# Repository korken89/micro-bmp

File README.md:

# Micro Black Magic Probe (µBMP)

A small [Black Magic Probe](https://github.com/blacksphere/blackmagic) based on the pinout of the STLink V2 support firmware. Connections has been added for the support of SWO, while the UART pinout is also available. Designed to stick directly into a USB port, without cable.

## Changes

### v1.4.1

* Reinforced the USB-C plug's mounting pads

### v1.4

* Changed to USB-C plug

### v1.3

* Added LED on the 5V line to see when the fuse is "blown"
* Removed panelized boards, to be updated later

### v1.2

* Removed component designators to clean up the PCB, the designators are available in the Gerbers
* Consolidated components, using resistor arrays and 8ch ESD/EMI filter
* Now have ESD/EMI protection on the outputs
* Added fuse of 5V line

### v1.0

* First release
* Tested and working

## Resources

### Schematics

A PDF print of the schematic are available in `ubmp_v1_3.pdf`.

### Programming instructions

Clone and build `stlink` unless you already have it:

```bash
cd ~/git
git clone --recursive https://github.com/texane/stlink
cd stlink
make -j4
```

Clone and build the firmware for `Black Magic Probe`, note to use `stlink` as `PROBE_HOST`:

```bash
cd ~/git
git clone --recursive https://github.com/blacksphere/blackmagic.git
cd blackmagic
cd libopencm3
make -j4 lib
cd ../src
make -j4 PROBE_HOST=stlink
```

Flash the `uBMP`:

```bash
cp ../../stlink/build/Release/st-flash .
./st-flash erase
./st-flash write blackmagic_dfu.bin 0x8000000
./st-flash --reset write blackmagic.bin 0x8002000
```

## Images

### USB-C version (v1.4)

### Second batch (v1.2)

### First batch (v1.0)

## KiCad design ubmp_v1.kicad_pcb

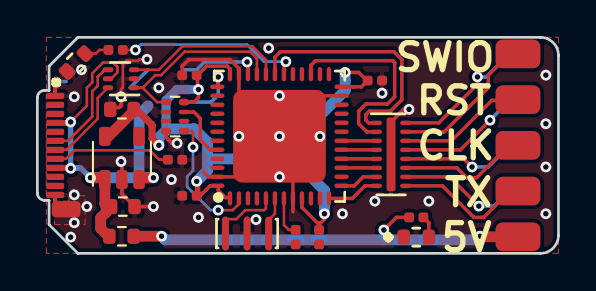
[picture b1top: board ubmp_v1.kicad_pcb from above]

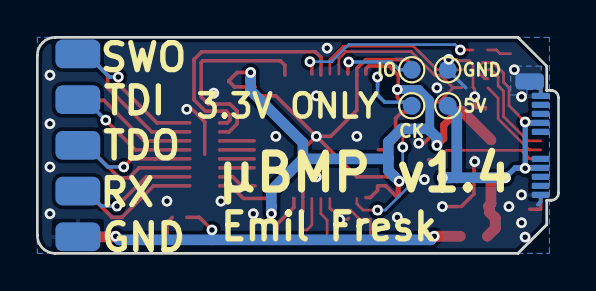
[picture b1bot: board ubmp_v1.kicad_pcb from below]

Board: 2 copper layers, 29.0 x 12.0 mm, 25 parts (4 on the bottom side), 35 nets.

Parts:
C1, C3, C4, C6, C7: 100n; C_0402_1005Metric_Rounded
C2, C5: 4.7u; C_0603_1608Metric_Rounded
D1, D2: LTST-C191KGKT; LEDC1608X60
F1: MF-FSMF050X-2; R_0603_1608Metric_Rounded
J1: M20-9760542; 2x5_2.54mm_side
P1: USB_C_Plug; USB_C_Plug_Molex_1054440001
R1, R2: 470; R_0402_1005Metric_Rounded
R3: 5.1k; R_0402_1005Metric_Rounded
RN1: EXB-28V152JX; R_Array_Convex_4x0402
TP1, TP2, TP3, TP4: Test_Point; TestPoint_Pad_D1.0mm
U1: NUF8401MNT4G; DFN-16-1EP_1.6x4mm_P0.5mm
U2: MIC5245-3.3YM5; SOT-23-5
U3: STM32F103CBU6; QFN-48-1EP_7x7mm_P0.5mm_EP5.15x5.15mm
U4: NUF2042XV6T1G; DFN-6-1EP_1.2x1.6mm_P0.5mm
Y1: PRQC8.00CR1010V00L; Resonator_3pin_3.2x1.3mm

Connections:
+3V3: C3.1, C4.1, C5.1, C6.1, C7.1, RN1.4, U2.5, U3.1, U3.9, U3.24, U3.36, U3.48
+5V: C2.1, F1.2, P1.A4, P1.A9, P1.B4, P1.B9, TP4.1, U2.1, U2.3, U4.5
/DM: P1.A7, U4.4
/DP: P1.A6, U4.6
/bmp_core/BMP_RST: U1.3, U3.18
/bmp_core/BMP_RSTo: J1.4, U1.14
/bmp_core/BMP_RX: U1.7, U3.13
/bmp_core/BMP_RXo: J1.9, U1.10
/bmp_core/BMP_SWCLK_TCK: U1.6, U3.15
/bmp_core/BMP_SWCLK_TCKo: J1.3, U1.11
/bmp_core/BMP_SWDIO_TMS: U1.2, U3.27
/bmp_core/BMP_SWDIO_TMSo: J1.5, U1.15
/bmp_core/BMP_SWO: U1.1, U3.31
/bmp_core/BMP_SWOo: J1.6, U1.16
/bmp_core/BMP_TDI: U1.4, U3.17
/bmp_core/BMP_TDIo: J1.7, U1.13
/bmp_core/BMP_TDO: U1.5, U3.16
/bmp_core/BMP_TDOo: J1.8, U1.12
/bmp_core/BMP_TX: U1.8, U3.12
/bmp_core/BMP_TXo: J1.2, U1.9
/bmp_core/BOOT0: RN1.3, U3.44
/bmp_core/DM_P: U3.32, U4.3
/bmp_core/DP_P: RN1.5, U3.33, U4.1
/bmp_core/LED_STLINK: R1.1, U3.30
/bmp_core/NRST: C1.2, U3.7
/bmp_core/STM_ID: RN1.1, U3.2
/bmp_core/SWCLK: TP2.1, U3.37
/bmp_core/SWDIO: TP1.1, U3.34
GND: C1.1, C2.2, C3.2, C4.2, C5.2, C6.2, C7.2, D1.1, D2.1, J1.10, P1.A1, P1.A12, P1.B1, P1.B12, P1.S1, R3.2, RN1.6, RN1.7, RN1.8, TP3.1, U1.17, U2.2, U3.8, U3.23, U3.35, U3.47, U3.49, U4.2, Y1.2
unnamed: D1.2, R1.2
unnamed: D2.2, R2.2
unnamed: F1.1, J1.1, R2.1
unnamed: P1.A5, R3.1
unnamed: U3.5, Y1.1
unnamed: U3.6, Y1.3

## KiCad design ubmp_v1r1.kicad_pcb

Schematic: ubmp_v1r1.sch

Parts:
C1, C2, C3, C4, C7: 100n; C_0402_1005Metric_Rounded
C5, C6: 4.7u; C_0603_1608Metric_Rounded
D2: GREEN; D_0603_1608Metric_Rounded
F1: MF-FSMF050X-2; R_0603_1608Metric_Rounded
J1: Conn_02x05_Counter_Clockwise; 2x5_2.54mm_side
J2: USB_A; USB_A_1001-011-01101
R1, R3, R4, R5, R10, R11, R12, R13: 100; R_0402_1005Metric_Rounded
R2: 470; R_0402_1005Metric_Rounded
R7, R8, R14, R17, R18, R19: 1.5k; R_0402_1005Metric_Rounded
R9, R15, R16: 22; R_0402_1005Metric_Rounded
TP1, TP2, TP3, TP4: Test_Point; TestPoint_Pad_D1.0mm
U1: STM32F103CBUx; QFN-48-1EP_7x7mm_P0.5mm_EP5.15x5.15mm
U2: MIC5245-3.3; SOT-23-5_Rounded
Y1: PRQC8.00CR1010V00L; Resonator_3pin_3.2x1.3mm

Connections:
+3V3: C1.1, C2.1, C3.1, C4.1, C6.1, R14.1, R17.1, U1.1, U1.9, U1.24, U1.36, U1.48, U2.5 (OUT)
+5V: C5.1, F1.2, J2.1, TP4.1, U2.1 (IN), U2.3 (EN)
/BMP_RST: R9.2, U1.18
/BMP_RSTo: J1.7, R9.1
/BMP_RX: R4.2, U1.13
/BMP_RXo: J1.9, R4.1
/BMP_SWCLK_TCK: R11.1, U1.15, U1.26
/BMP_SWCLK_TCKo: J1.3, R11.2
/BMP_SWDIO_TMS: R1.2, R13.1, U1.27
/BMP_SWDIO_TMSo: J1.5, R13.2
/BMP_SWO: R10.1, U1.31
/BMP_SWOo: J1.6, R10.2
/BMP_TDI: R5.2, U1.17
/BMP_TDIo: J1.4, R5.1
/BMP_TDO: R12.1, U1.16
/BMP_TDOo: J1.8, R12.2
/BMP_TX: R3.2, U1.12
/BMP_TXo: J1.2, R3.1
/BOOT0: R7.1, U1.44
/DM: J2.2, R15.1
/DM_P: R15.2, U1.32
/DP: J2.3, R14.2, R16.1
/DP_P: R16.2, U1.33
/LED_STLINK: R2.1, U1.30
/NRST: C7.2, U1.7
/STLINK_AIN_1: R17.2, R18.2, U1.10
/STLINK_SWDIO_IN: R1.1, U1.25
/STM_ID: R8.1, U1.2
/STM_ID2: R19.1, U1.3
/SWCLK: TP2.1, U1.37
/SWDIO: TP1.1, U1.34
GND: C1.2, C2.2, C3.2, C4.2, C5.2, C6.2, C7.1, D2.1, J1.10, J2.4, J2.5, R7.2, R8.2, R18.1, R19.2, TP3.1, U1.8, U1.20, U1.23, U1.35, U1.47, U1.49, U2.2 (GND), Y1.2
unnamed: D2.2, R2.2
unnamed: F1.1, J1.1
unnamed: U1.5, Y1.1
unnamed: U1.6, Y1.3

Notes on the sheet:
STLink V2 identifier (PC13 = 0)
RST resistor is 22 Ohm to support board with small (<1.5k) pullup on RST
µBMP
2018-02-16
1.0
SWD Programming
MCO
Note that this board is designed to work with the STLink V2 version of Black Magic Probe firmware.
Design available at: github.com/korken89/micro-bmp
STLink compatibility

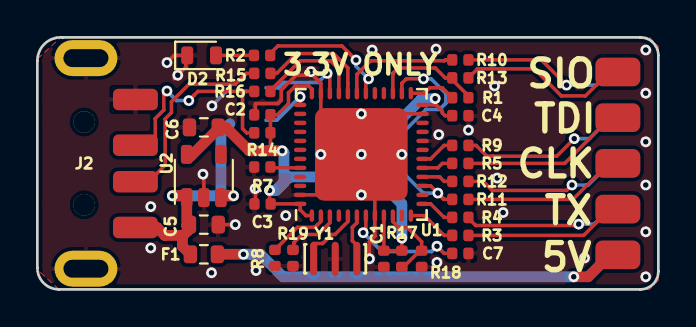
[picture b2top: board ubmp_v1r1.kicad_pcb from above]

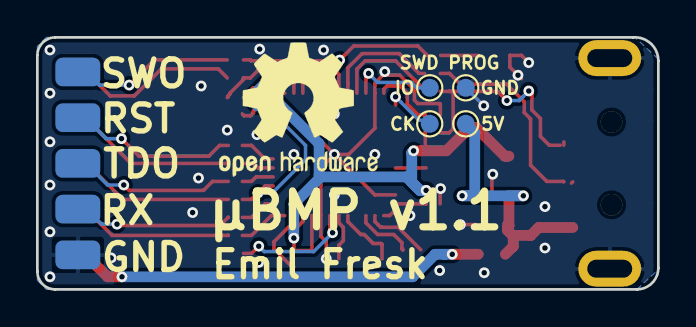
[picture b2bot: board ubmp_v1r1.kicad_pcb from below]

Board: 2 copper layers, 34.5 x 14.0 mm, 36 parts (4 on the bottom side), 36 nets.

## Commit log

2018-02-05 PCB layout
2018-02-05 PCB layout done
2018-02-05 Added text to PCB
2018-02-05 Added OSHW + README
2018-02-05 More GND
2018-02-05 Minor silk fix
2018-02-06 Updated schematic for STLink V2 clone
2018-02-06 Updated board for STLink V2 clone, added schematic print, updated images, updated README
2018-02-06 Clean up
2018-02-06 Added SWD PROG text
2018-02-06 Added gerbers
2018-02-08 Minor improvements
2018-02-08 Added link to BMP git
2018-02-09 Added size text and regenerated gerbers
2018-02-09 Fixed corners and updated images
2018-02-09 Changed placement of OSHW logo
2018-02-09 Updated fab layer
2018-02-11 Made pour outline follow board outline
2018-02-11 Tested making a 4x3 panel
2018-02-11 Testing more with panel
2018-02-12 Added size to panel
2018-02-12 Fixed rounded pads and bad soldermask width on 0402
2018-02-12 Silk fix
2018-02-17 Updated USB footprint
2018-02-17 Fixed footprint associations in sch
2018-02-17 Updated gerbers
2018-02-17 Footprint fixes
2018-02-17 Added script to rename gerbers
2018-02-17 Updated images
2018-02-18 Changed to USB connector, 1.6mm PCB was too thin
2018-03-24 Added images for mounted uBMP + added flash instructions
2018-03-25 Now more compatible with STLink-v2
    Changes:
    * Fixed 0603 cap spacing
    * Added fuse to 5V line
    * Connected unused signals from STLink schematic
    * Connected BOOT1 to GND
    * Removed yellow LED
2018-03-25 Updated PCB version number, generated new schematic
2018-03-26 Updated reset circuit and updated silkscreen layout
2018-03-26 Updated schematic PDF and removed renders from README
2018-03-26 Regenerated gerbers to include slots in USB connector
2018-03-26 Bumped version number
2018-03-26 Reverted STlink compatibility changes and updated a lot of footprints
2018-03-26 Regernerated gerbers
2018-03-27 Renamed and added USBPCB version as seperate project
2018-03-27 Regenerated gerbers
2018-03-27 Bumped schematic date
2018-03-28 Changed all 100 and 22 ohm resistors to ESD chips with built in resistors
2018-03-29 Added ESD lib
2018-03-29 Split into hierarchical sheep
2018-03-29 Updated pinput
2018-03-30 Moved libs to external repo
2018-03-30 Updated PCB USB version
2018-03-30 Updated gitignore
2018-03-30 Updated fp-lib-table
2018-03-30 Updated PCB locks and panel
2018-03-30 Updated 3d kicad_libs
2018-03-31 Updated components + libs and changed to 1.5k resistor arrary
2018-03-31 Minor PCB fixes, added OSHW logo
2018-03-31 Updated USBPCB version and panel
2018-04-01 Improved ground layout
2018-04-01 Fixed through holes on USB connector to be NPTH
2018-04-02 Updated part numbers
2018-04-02 Regenerated PDF schematic
2018-04-02 Improved resistor array pad sizes
2018-04-03 Bumped schematic date and added value to resistor array
2018-04-04 Updated kicad_libs
2018-04-14 Update 0402 and 0603 to IPC least
2018-04-15 Added OSHW logo
2018-04-15 Updated panel for hand assembly
2018-11-18 v1.3 release
2019-01-03 Moved to USB-C plug
2019-01-03 Added image to README of v1.4
2019-01-03 Updated gitignore to not add gerbers folder
2019-01-03 Reinforced the USB-C anchor pads
2019-01-03 Updated readme for v1.4.1
2019-01-15 Improved USB-C mounting even more
2019-01-15 Fixed corners to better fit the USB-C connector
